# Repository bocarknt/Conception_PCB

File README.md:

# Conception PCB – STM32F031K6T7 Système Embarqué

Carte PCB personnalisée conçue pour un nœud IoT embarqué basé sur le microcontrôleur **STM32F031K6T7**. Réalisée avec **KiCad** dans le cadre d'un cours de conception de PCB pour systèmes embarqués.

---

## Vue d'ensemble

| Paramètre | Valeur |
|-----------|--------|
| Microcontrôleur | STM32F031K6T7 |
| Dimensions | 53 × 22,5 mm |
| Alimentation | 12V / 5V |
| Tension régulée | 3,3V (régulateur embarqué) |
| Cristal | 8 MHz |

---

## Connecteurs

| Connecteur | Type | Fonction |
|------------|------|----------|
| J1 | Grove (4 broches) | Capteur – I2C |
| J2 | Header mâle | Communication – UART (FT232) |
| J3 | Header mâle | Programmateur SWD (ST-Link CN4) |
| J4 | Borne à vis | Alimentation (12V / 5V) |

---

## Capteur – SHT31

Capteur de température et d'humidité compatible Grove.

| Paramètre | Valeur |
|-----------|--------|
| Interface | I2C |
| Alimentation | 3,3V |
| Plage de température | -40°C à +125°C |
| Plage d'humidité | 0–100 %HR |

---

## Communication – FT232 (USB-UART)

Le module basé sur le **FT232R** se connecte à **J2** via UART et fournit une interface série USB vers un ordinateur hôte.

| Broche MCU | Signal | Broche J2 |
|------------|--------|-----------|
| PA9 (TX) | → RX | FT232 RX |
| PA10 (RX) | ← TX | FT232 TX |
| — | GND | GND |
| — | VCC (3,3V) | VCC |

---

## Programmation – ST-Link via J3 (SWD)

| Broche J3 | Signal | Description |
|-----------|--------|-------------|
| 1 | VDD_TARGET | 3,3V de la carte |
| 2 | SWCLK | Horloge SWD |
| 3 | GND | Masse |
| 4 | SWDIO | Données SWD |
| 5 | NRST | Réinitialisation |
| 6 | SWO | Réservé |

Outils utilisés : **STM32CubeIDE** + **STM32 ST-Link Utility**

Commande de flashage :
```
-c SWD -p ${project_loc}\Debug\${project_name}.hex -v -Rst
```

---

## Composants embarqués

| Composant | Fonction |
|-----------|----------|
| LED Verte | Sortie numérique (GPIO) |
| RST | Bouton poussoir – Réinitialisation |
| Y1 | Cristal 8 MHz |
| U2 | Régulateur de tension 3,3V |

---

## Structure du dépôt

```
├── README.md
├── kicad/
│   ├── projet.kicad_sch       # Schématique
│   └── projet.kicad_pcb       # Routage PCB
└── media/
    ├── pcb_top.png           # Photo vue dessus
    ├── pcb_bottom.png         # Photo vue dessous
    ├── carte_pcb.jpeg         #photo de la carte avec les composants soudés
    ├── schema.png             #capture du Schématique
    ├── routage.png            # capture du routage
    └── demo.mp4               # Vidéo de démonstration
```

---

## Outils

- [KiCad](https://www.kicad.org/) – Conception schématique et PCB
- [STM32CubeIDE](https://www.st.com/en/development-tools/stm32cubeide.html) – Développement firmware
- [STM32 ST-Link Utility](https://www.st.com/en/development-tools/stsw-link004.html) – Flashage

---

## Références

- [Fiche technique SHT31](https://raw.githubusercontent.com/SeeedDocument/Grove-TempAndHumi_Sensor-SHT31/master/res/Grove-TempAndHumi_Sensor-SHT31-Datasheets.zip)
- [Fiche technique FT232R – FTDI](https://ftdichip.com/wp-content/uploads/2020/08/DS_FT232R.pdf)
- [Fiche technique STM32F031K6 – ST](https://www.st.com/en/microcontrollers-microprocessors/stm32f031k6.html)
- [Connecteur SWD CN4 Nucleo – ST UM1724](https://www.st.com/resource/en/user_manual/um1724-stm32-nucleo64-boards-mb1136-stmicroelectronics.pdf)

---

## Photos de la carte

---

## Démonstration

https://github.com/bocarknt/Conception_PCB/blob/main/media/demo.mp4

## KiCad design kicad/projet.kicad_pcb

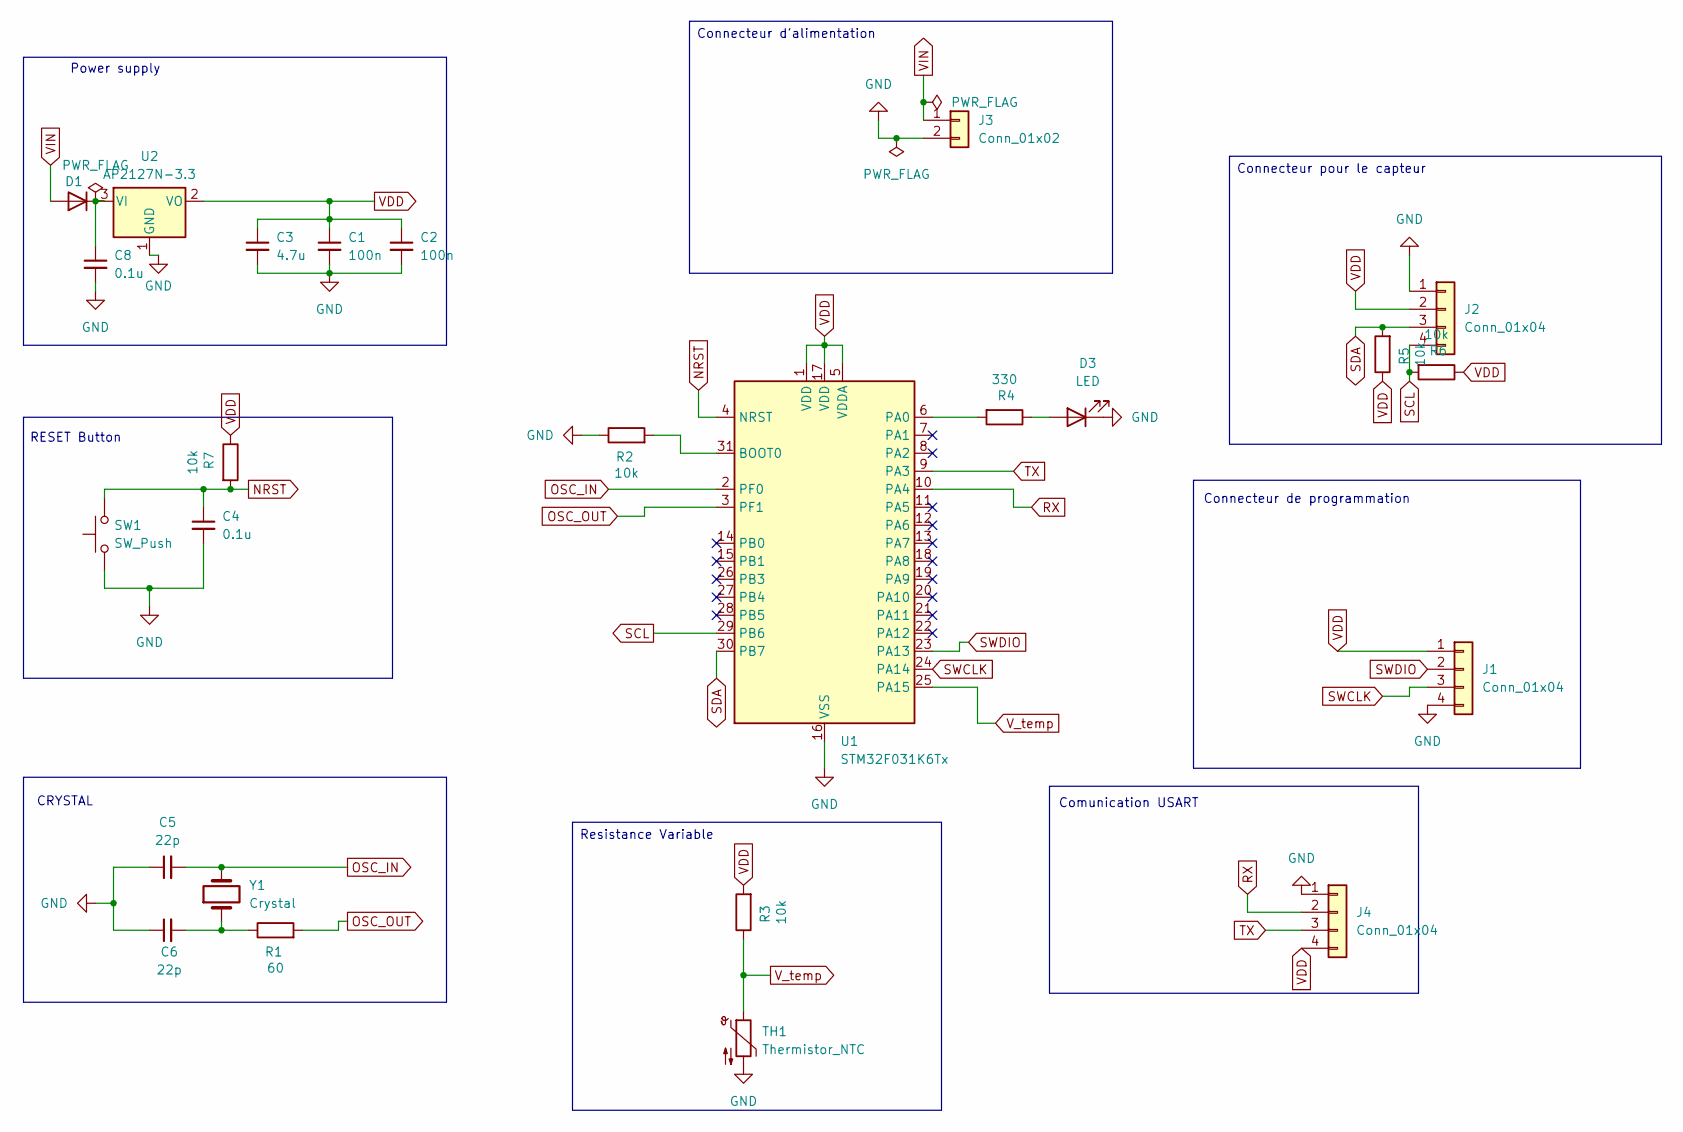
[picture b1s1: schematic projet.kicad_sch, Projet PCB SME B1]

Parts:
C1, C2: 100n; C_0805_2012Metric_Pad1.18x1.45mm_HandSolder
C3: 4.7u; C_0805_2012Metric_Pad1.18x1.45mm_HandSolder
C4, C8: 0.1u; C_0805_2012Metric_Pad1.18x1.45mm_HandSolder
C5, C6: 22p; C_0805_2012Metric_Pad1.18x1.45mm_HandSolder
D1: D_DO-35_SOD27_P7.62mm_Horizontal
D3: LED; LED_D3.0mm
J1, J4: Conn_01x04; PinHeader_1x04_P2.54mm_Vertical
J2: Conn_01x04; NS-Tech_Grove_1x04_P2mm_Vertical
J3: Conn_01x02; PinHeader_1x02_P2.54mm_Vertical
R1: 60; R_0805_2012Metric_Pad1.20x1.40mm_HandSolder
R2, R3, R5, R6, R7: 10k; R_0805_2012Metric_Pad1.20x1.40mm_HandSolder
R4: 330; R_0805_2012Metric_Pad1.20x1.40mm_HandSolder
SW1: SW_Push; SW_PUSH_6mm_H5mm
TH1: Thermistor_NTC; R_0805_2012Metric_Pad1.20x1.40mm_HandSolder
U1: STM32F031K6Tx; LQFP-32_7x7mm_P0.8mm
U2: AP2127N-3.3; SOT-23
Y1: Crystal; Crystal_HC49-4H_Vertical

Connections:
GND: C1.2, C2.2, C3.2, C4.2, C5.1, C6.1, C8.2, D3.1 (K), J1.4, J2.1, J3.2, J4.1, R2.1, SW1.1, TH1.2, U1.16 (VSS), U1.32 (VSS), U2.1 (GND)
NRST: C4.1, R7.2, SW1.2, U1.4 (NRST)
unnamed: C6.2, R1.1, Y1.1
unnamed: C8.1, D1.1 (K), U2.3 (VI)
unnamed: D3.2 (A), R4.1
unnamed: R2.2, U1.31 (BOOT0)
unnamed: R4.2, U1.6 (PA0)
OSC_IN: C5.2, U1.2 (PF0), Y1.2
OSC_OUT: R1.2, U1.3 (PF1)
RX: J4.2, U1.10 (PA4)
SCL: J2.4, R6.2, U1.29 (PB6)
SDA: J2.3, R5.2, U1.30 (PB7)
SWCLK: J1.3, U1.24 (PA14)
SWDIO: J1.2, U1.23 (PA13)
TX: J4.3, U1.9 (PA3)
VDD: C1.1, C2.1, C3.1, J1.1, J2.2, J4.4, R3.2, R5.1, R6.1, R7.1, U1.1 (VDD), U1.5 (VDDA), U1.17 (VDD), U2.2 (VO)
VIN: D1.2 (A), J3.1
V_temp: R3.1, TH1.1, U1.25 (PA15)

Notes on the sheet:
Connecteur de programmation
RESET Button
Power supply
CRYSTAL
Comunication USART
Connecteur d'alimentation
Resistance Variable
Connecteur pour le capteur

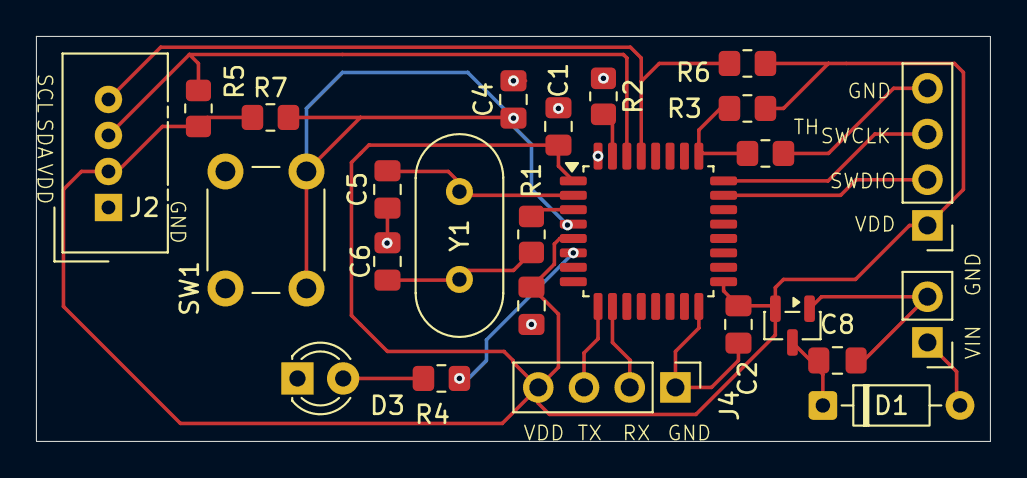
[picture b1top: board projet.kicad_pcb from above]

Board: 2 copper layers, 53.0 x 22.5 mm, 25 parts (0 on the bottom side), 18 nets.

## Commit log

2026-06-03 Mise à jour
2026-06-03 Fix image filename for 'Carte prete' in README
2026-06-03 Update SHT31 datasheet link in README
2026-06-03 Fix reference link for SHT31 datasheet
2026-06-03 Enhance media section with image descriptions
    Added descriptions for images in media section.
2026-06-03 Update KiCad version in README
